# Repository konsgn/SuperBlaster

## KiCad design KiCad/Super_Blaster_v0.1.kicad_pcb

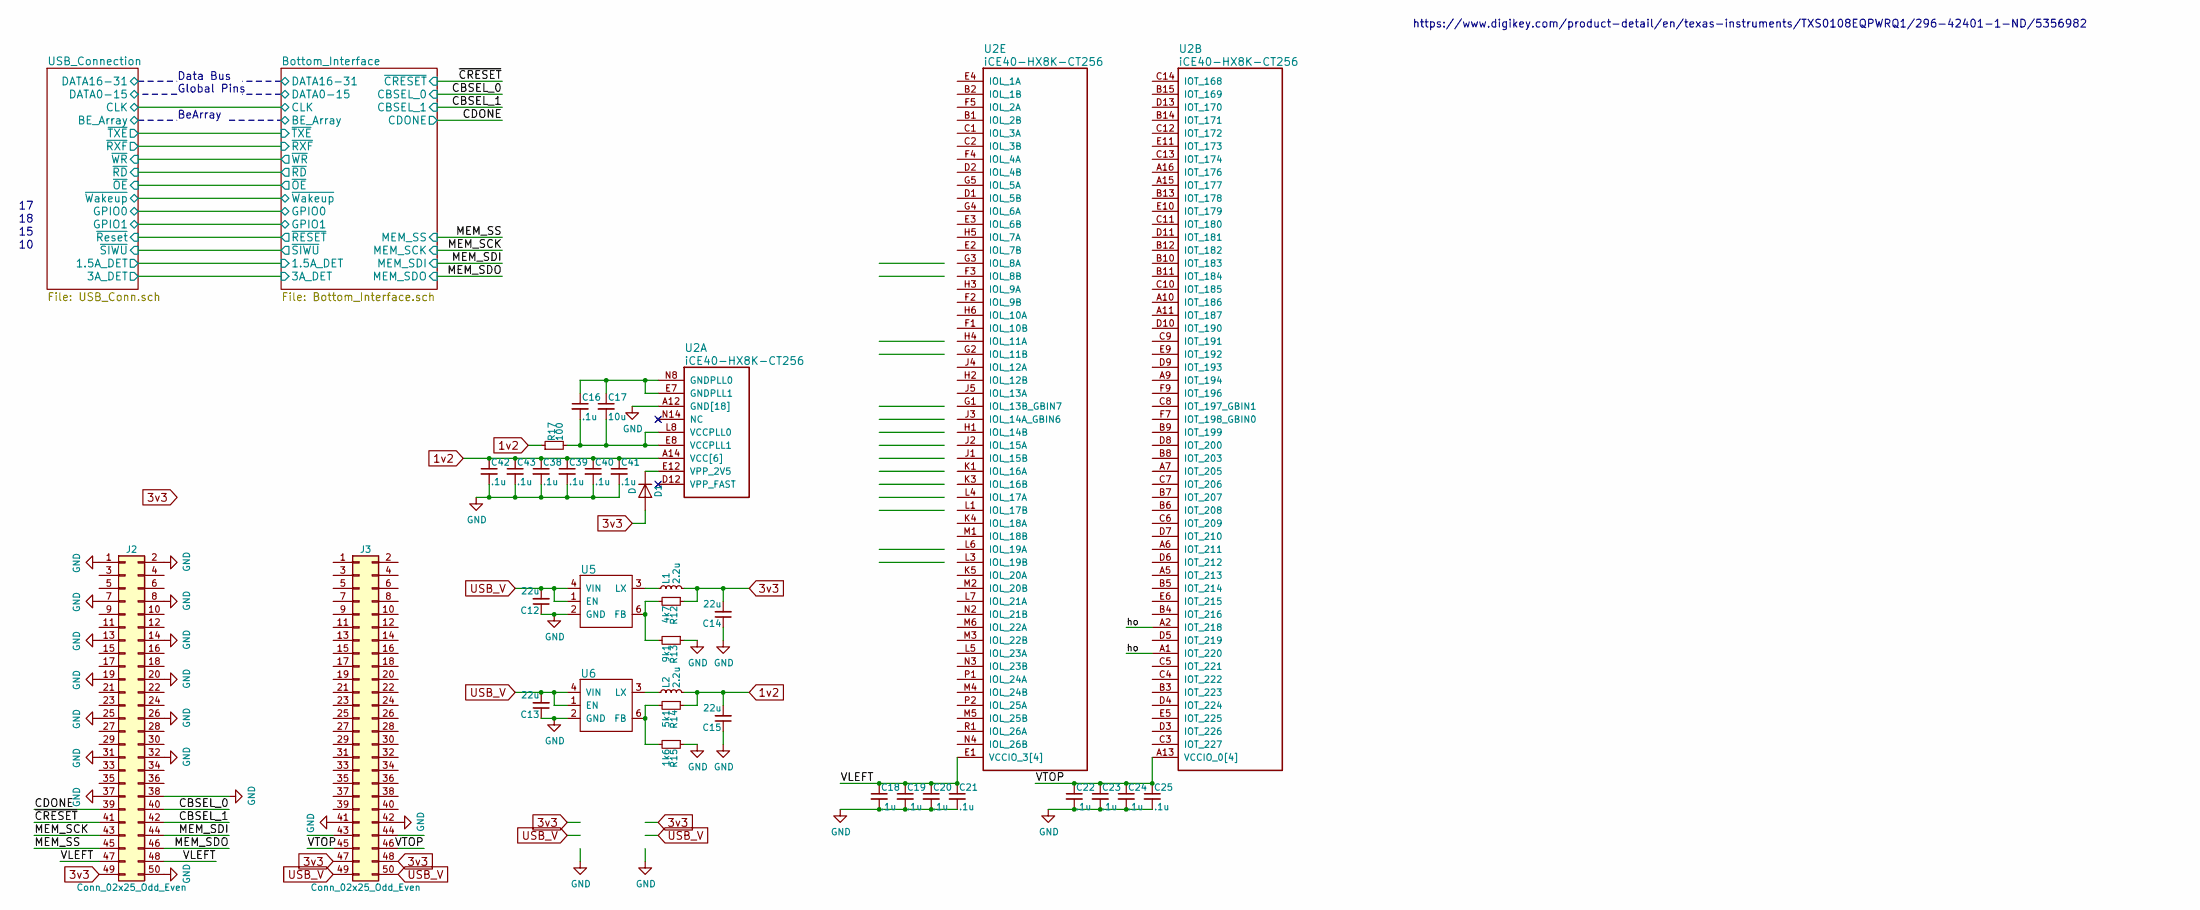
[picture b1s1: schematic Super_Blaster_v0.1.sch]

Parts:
C12, C13, C14, C15: 22u; C_0603
C16, C18, C19, C20, C21, C22, C23, C24, C25, C38, C39, C40, C41, C42, C43: .1u; C_0402_NoSilk
C17: 10u; C_0603
D1: D; D_0402_1005Metric
J2, J3: Conn_02x25_Odd_Even; Pin_Header_Straight_2x25_Pitch1.27mm_tight_SMD
L1, L2: 2.2u; L_1008
R12: 4k7; R_0402
R13: 9k1; R_0402
R14: 5k1; R_0402
R15: 1k6; R_0402
R17: 100; R_0603
U2: iCE40-HX8K-CT256; caBGA_256_.8p_14x14mm
U5, U6: REG_EN_GND_LX_VIN_NC_FB; TSOT-23-6

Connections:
1v2: C15.2, C38.1, C39.1, C40.1, C41.1, C42.1, C43.1, L2.2, R14.1, R17.1, U2.A14 (VCC[6]), U2.F6 (VCC[6]), U2.F10 (VCC[6]), U2.K6 (VCC[6]), U2.K10 (VCC[6]), U2.L2 (VCC[6])
3v3: C14.2, D1.2 (A), J2.49, J3.47, J3.48, L1.2, R12.1; also elsewhere on the board
/CBSEL_0: J2.40; also elsewhere on the board
/CBSEL_1: J2.42; also elsewhere on the board
/CDONE: J2.39; also elsewhere on the board
/MEM_SCK: J2.43; also elsewhere on the board
/MEM_SDI: J2.44; also elsewhere on the board
/MEM_SDO: J2.46; also elsewhere on the board
/MEM_SS: J2.45; also elsewhere on the board
/VLEFT: C18.1, C19.1, C20.1, C21.1, J2.47, J2.48, U2.E1 (VCCIO_3[4]), U2.G6 (VCCIO_3[4]), U2.J6 (VCCIO_3[4]), U2.N1 (VCCIO_3[4])
/VTOP: C22.1, C23.1, C24.1, C25.1, J3.45, J3.46, U2.A3 (VCCIO_0[4]), U2.A8 (VCCIO_0[4]), U2.A13 (VCCIO_0[4]), U2.F8 (VCCIO_0[4])
/ho: U2.A1 (IOT_220), U2.A2 (IOT_218)
/~CRESET: J2.41; also elsewhere on the board
GND: C12.1, C13.1, C14.1, C15.1, C18.2, C19.2, C20.2, C21.2, C22.2, C23.2, C24.2, C25.2, C38.2, C39.2, C40.2, C41.2, C42.2, C43.2, J2.1, J2.2, J2.7, J2.8, J2.13, J2.14, J2.19, J2.20, J2.25, J2.26, J2.31, J2.32, J2.37, J2.38, J2.50, J3.41, J3.42, R13.1, R15.1, U2.A4 (GND[18]), U2.A12 (GND[18]), U2.E15 (GND[18]), U2.G7 (GND[18]), U2.G8 (GND[18]), U2.G9 (GND[18]), U2.H7 (GND[18]), U2.H8 (GND[18]), U2.H9 (GND[18]), U2.J7 (GND[18]), U2.J8 (GND[18]), U2.J9 (GND[18]), U2.K2 (GND[18]), U2.K7 (GND[18]), U2.L15 (GND[18]), U2.R7 (GND[18]), U2.T4 (GND[18]), U2.T12 (GND[18]), U5.2 (GND), U6.2 (GND); also elsewhere on the board
unnamed: C16.1, C17.1, U2.E7 (GNDPLL1), U2.N8 (GNDPLL0)
unnamed: C16.2, C17.2, R17.2, U2.E8 (VCCPLL1), U2.L8 (VCCPLL0)
unnamed: D1.1 (K), U2.E12 (VPP_2V5)
unnamed: L1.1, U5.3 (LX)
unnamed: L2.1, U6.3 (LX)
unnamed: R12.2, R13.2, U5.6 (FB)
unnamed: R14.2, R15.2, U6.6 (FB)
USB_V: C12.2, C13.2, J3.49, J3.50, U5.1 (EN), U5.4 (VIN), U6.1 (EN), U6.4 (VIN); also elsewhere on the board

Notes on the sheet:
BeArray
Data Bus Global Pins
https://www.digikey.com/product-detail/en/texas-instruments/TXS0108EQPWRQ1/296-42401-1-ND/5356982

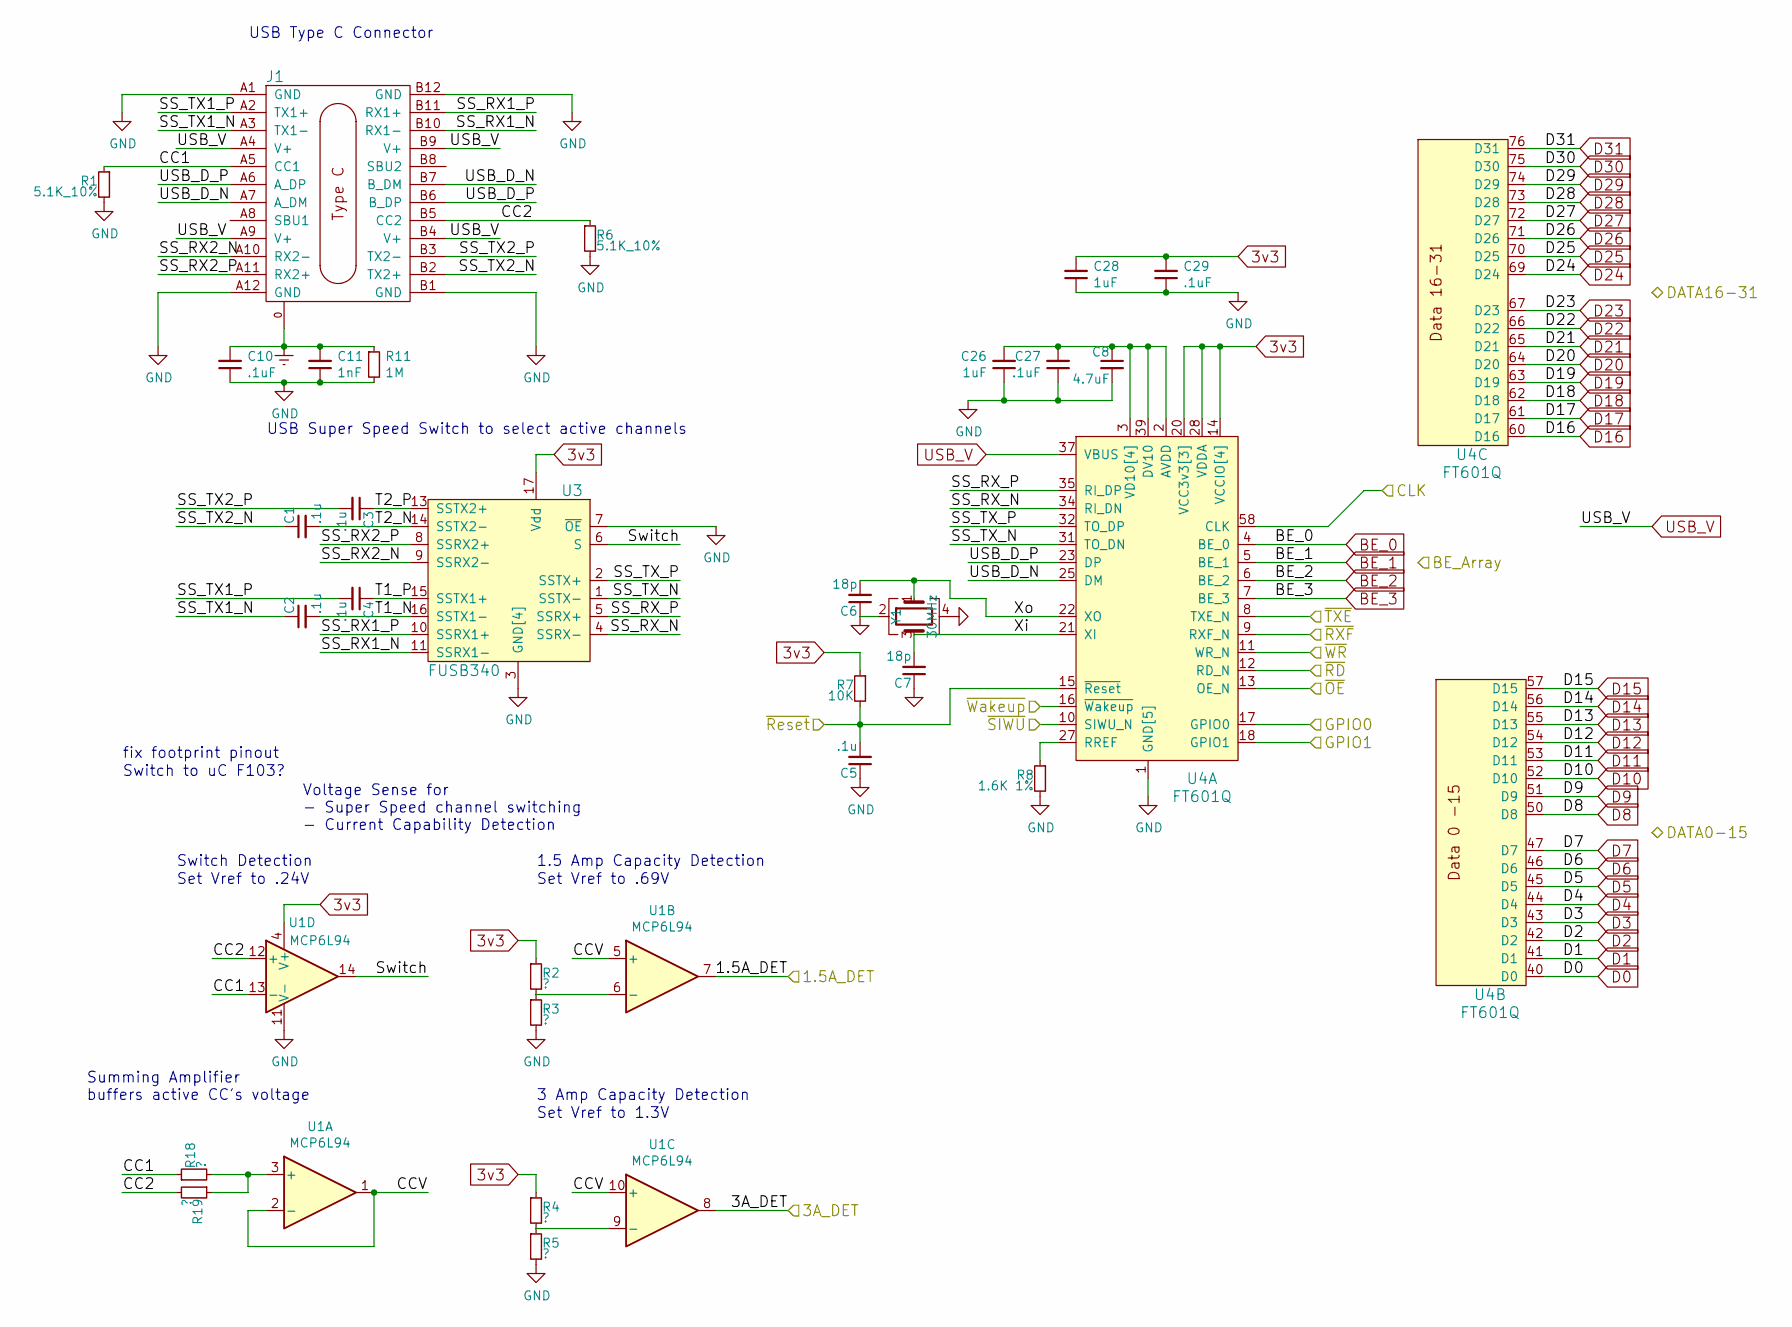
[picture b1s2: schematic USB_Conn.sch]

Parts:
C1, C2, C3, C4, C5: .1u; C_0402
C6, C7: 18p; C_0402
C8: 4.7uF; C_0603
C10, C27, C29: .1uF; C_0402
C11: 1nF; C_0402
C26, C28: 1uF; C_0402
J1: USB_TypeC_AMP_12401610E4#2A; USB_TypeC_Right_Angle_SMD_THT_12401610E4#2A
R1, R6: 5.1K_10%; R_0402
R2, R3, R4, R5, R18, R19: ?; R_0402
R7: 10K; R_0402
R8: 1.6K 1%; R_0402
R11: 1M; R_0402
U1: MCP6L94; SSOP-14
U3: FUSB340; FUSB340_Custom
U4: FT601Q; QFN_76_PAD
Y1: 30MHz; Crystal_SMD_2016-4Pin_2.0x1.6mm; MPN XRCGB30M000F3M00R0

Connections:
3v3: C28.2, C29.2, R2.1, R4.1, R7.1, U1.4 (V+), U3.17 (Vdd), U4.14 (VCCIO[4]), U4.20 (VCC3v3[3]), U4.24 (VCC3v3), U4.28 (VDDA), U4.38 (VCC3v3), U4.49 (VCCIO), U4.59 (VCCIO), U4.68 (VCCIO); also elsewhere on the board
/Bottom_Interface/1.5A_DET: U1.7; also elsewhere on the board
/Bottom_Interface/3A_DET: U1.8; also elsewhere on the board
/Bottom_Interface/CLK: U4.58 (CLK); also elsewhere on the board
/Bottom_Interface/GPIO0: U4.17 (GPIO0); also elsewhere on the board
/Bottom_Interface/GPIO1: U4.18 (GPIO1); also elsewhere on the board
/Bottom_Interface/~OE: U4.13 (OE_N); also elsewhere on the board
/Bottom_Interface/~RD: U4.12 (RD_N); also elsewhere on the board
/Bottom_Interface/~RESET: C5.2, R7.2, U4.15 (~Reset); also elsewhere on the board
/Bottom_Interface/~RXF: U4.9 (RXF_N); also elsewhere on the board
/Bottom_Interface/~SIWU: U4.10 (SIWU_N); also elsewhere on the board
/Bottom_Interface/~TXE: U4.8 (TXE_N); also elsewhere on the board
/Bottom_Interface/~WR: U4.11 (WR_N); also elsewhere on the board
/Bottom_Interface/~Wakeup: U4.16 (~Wakeup); also elsewhere on the board
/USB_Connection/CC1: J1.A5 (CC1), R1.1, R18.1, U1.13 (-)
/USB_Connection/CC2: J1.B5 (CC2), R6.1, R19.2, U1.12 (+)
/USB_Connection/CCV: U1.1, U1.2 (-), U1.5 (+), U1.10 (+)
/USB_Connection/SS_RX1_N: J1.B10 (RX1-), U3.11 (SSRX1-)
/USB_Connection/SS_RX1_P: J1.B11 (RX1+), U3.10 (SSRX1+)
/USB_Connection/SS_RX2_N: J1.A10 (RX2-), U3.9 (SSRX2-)
/USB_Connection/SS_RX2_P: J1.A11 (RX2+), U3.8 (SSRX2+)
/USB_Connection/SS_RX_N: U3.4 (SSRX-), U4.34 (RI_DN)
/USB_Connection/SS_RX_P: U3.5 (SSRX+), U4.35 (RI_DP)
/USB_Connection/SS_TX1_N: C2.1, J1.A3 (TX1-)
/USB_Connection/SS_TX1_P: C4.2, J1.A2 (TX1+)
/USB_Connection/SS_TX2_N: C1.1, J1.B2 (TX2+)
/USB_Connection/SS_TX2_P: C3.2, J1.B3 (TX2-)
/USB_Connection/SS_TX_N: U3.1 (SSTX-), U4.31 (TO_DN)
/USB_Connection/SS_TX_P: U3.2 (SSTX+), U4.32 (TO_DP)
/USB_Connection/Switch: U1.14, U3.6 (S)
/USB_Connection/T1_N: C2.2, U3.16 (SSTX1-)
/USB_Connection/T1_P: C4.1, U3.15 (SSTX1+)
/USB_Connection/T2_N: C1.2, U3.14 (SSTX2-)
/USB_Connection/T2_P: C3.1, U3.13 (SSTX2+)
/USB_Connection/USB_D_N: J1.A7 (A_DM), J1.B7 (B_DM), U4.25 (DM)
/USB_Connection/USB_D_P: J1.A6 (A_DP), J1.B6 (B_DP), U4.23 (DP)
/USB_Connection/Xi: C7.2, U4.21 (XI), Y1.3
/USB_Connection/Xo: C6.2, U4.22 (XO), Y1.1
BE_0: U4.4 (BE_0); also elsewhere on the board
BE_1: U4.5 (BE_1); also elsewhere on the board
BE_2: U4.6 (BE_2); also elsewhere on the board
BE_3: U4.7 (BE_3); also elsewhere on the board
D0: U4.40 (D0); also elsewhere on the board
D1: U4.41 (D1); also elsewhere on the board
D2: U4.42 (D2); also elsewhere on the board
D3: U4.43 (D3); also elsewhere on the board
D4: U4.44 (D4); also elsewhere on the board
D5: U4.45 (D5); also elsewhere on the board
D6: U4.46 (D6); also elsewhere on the board
D7: U4.47 (D7); also elsewhere on the board
D8: U4.50 (D8); also elsewhere on the board
D9: U4.51 (D9); also elsewhere on the board
D10: U4.52 (D10); also elsewhere on the board
D11: U4.53 (D11); also elsewhere on the board
D12: U4.54 (D12); also elsewhere on the board
D13: U4.55 (D13); also elsewhere on the board
D14: U4.56 (D14); also elsewhere on the board
D15: U4.57 (D15); also elsewhere on the board
D16: U4.60 (D16); also elsewhere on the board
D17: U4.61 (D17); also elsewhere on the board
D18: U4.62 (D18); also elsewhere on the board
D19: U4.63 (D19); also elsewhere on the board
D20: U4.64 (D20); also elsewhere on the board
D21: U4.65 (D21); also elsewhere on the board
D22: U4.66 (D22); also elsewhere on the board
D23: U4.67 (D23); also elsewhere on the board
D24: U4.69 (D24); also elsewhere on the board
D25: U4.70 (D25); also elsewhere on the board
D26: U4.71 (D26); also elsewhere on the board
D27: U4.72 (D27); also elsewhere on the board
D28: U4.73 (D28); also elsewhere on the board
D29: U4.74 (D29); also elsewhere on the board
D30: U4.75 (D30); also elsewhere on the board
D31: U4.76 (D31); also elsewhere on the board
Earth: C10.2, C11.2, J1.0, R11.1
GND: C5.1, C6.1, C7.1, C8.2, C10.1, C11.1, C26.1, C27.1, C28.1, C29.1, J1.A1 (GND), J1.A12 (GND), J1.B1 (GND), J1.B12 (GND), R1.2, R3.2, R5.2, R6.2, R8.2, R11.2, U1.11 (V-), U3.3 (GND[4]), U3.7 (~OE), U3.12 (GND[4]), U3.18 (GND[4]), U3.PAD (GND[4]), U4.1 (GND[5]), U4.26 (GND), U4.29 (GND), U4.36 (GND), U4.77 (GND), Y1.2, Y1.4; also elsewhere on the board
unnamed: R2.2, R3.1, U1.6 (-)
unnamed: R4.2, R5.1, U1.9 (-)
unnamed: R8.1, U4.27 (RREF)
unnamed: R18.2, R19.1, U1.3 (+)
USB_V: J1.A4 (V+), J1.A9 (V+), J1.B4 (V+), J1.B9 (V+), U4.37 (VBUS); also elsewhere on the board
VD10: C8.1, C26.2, C27.2, U4.2 (AVDD), U4.3 (VD10[4]), U4.30 (VD10), U4.33 (VD10), U4.39 (DV10), U4.48 (VD10)

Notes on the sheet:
USB Type C Connector
USB Super Speed Switch to select active channels
Voltage Sense for - Super Speed channel switching - Current Capability Detection
Switch Detection
1.5 Amp Capacity Detection
3 Amp Capacity Detection
Set Vref to .69V
Set Vref to 1.3V
Set Vref to .24V
fix footprint pinout
Switch to uC F103?
Summing Amplifier buffers active CC's voltage

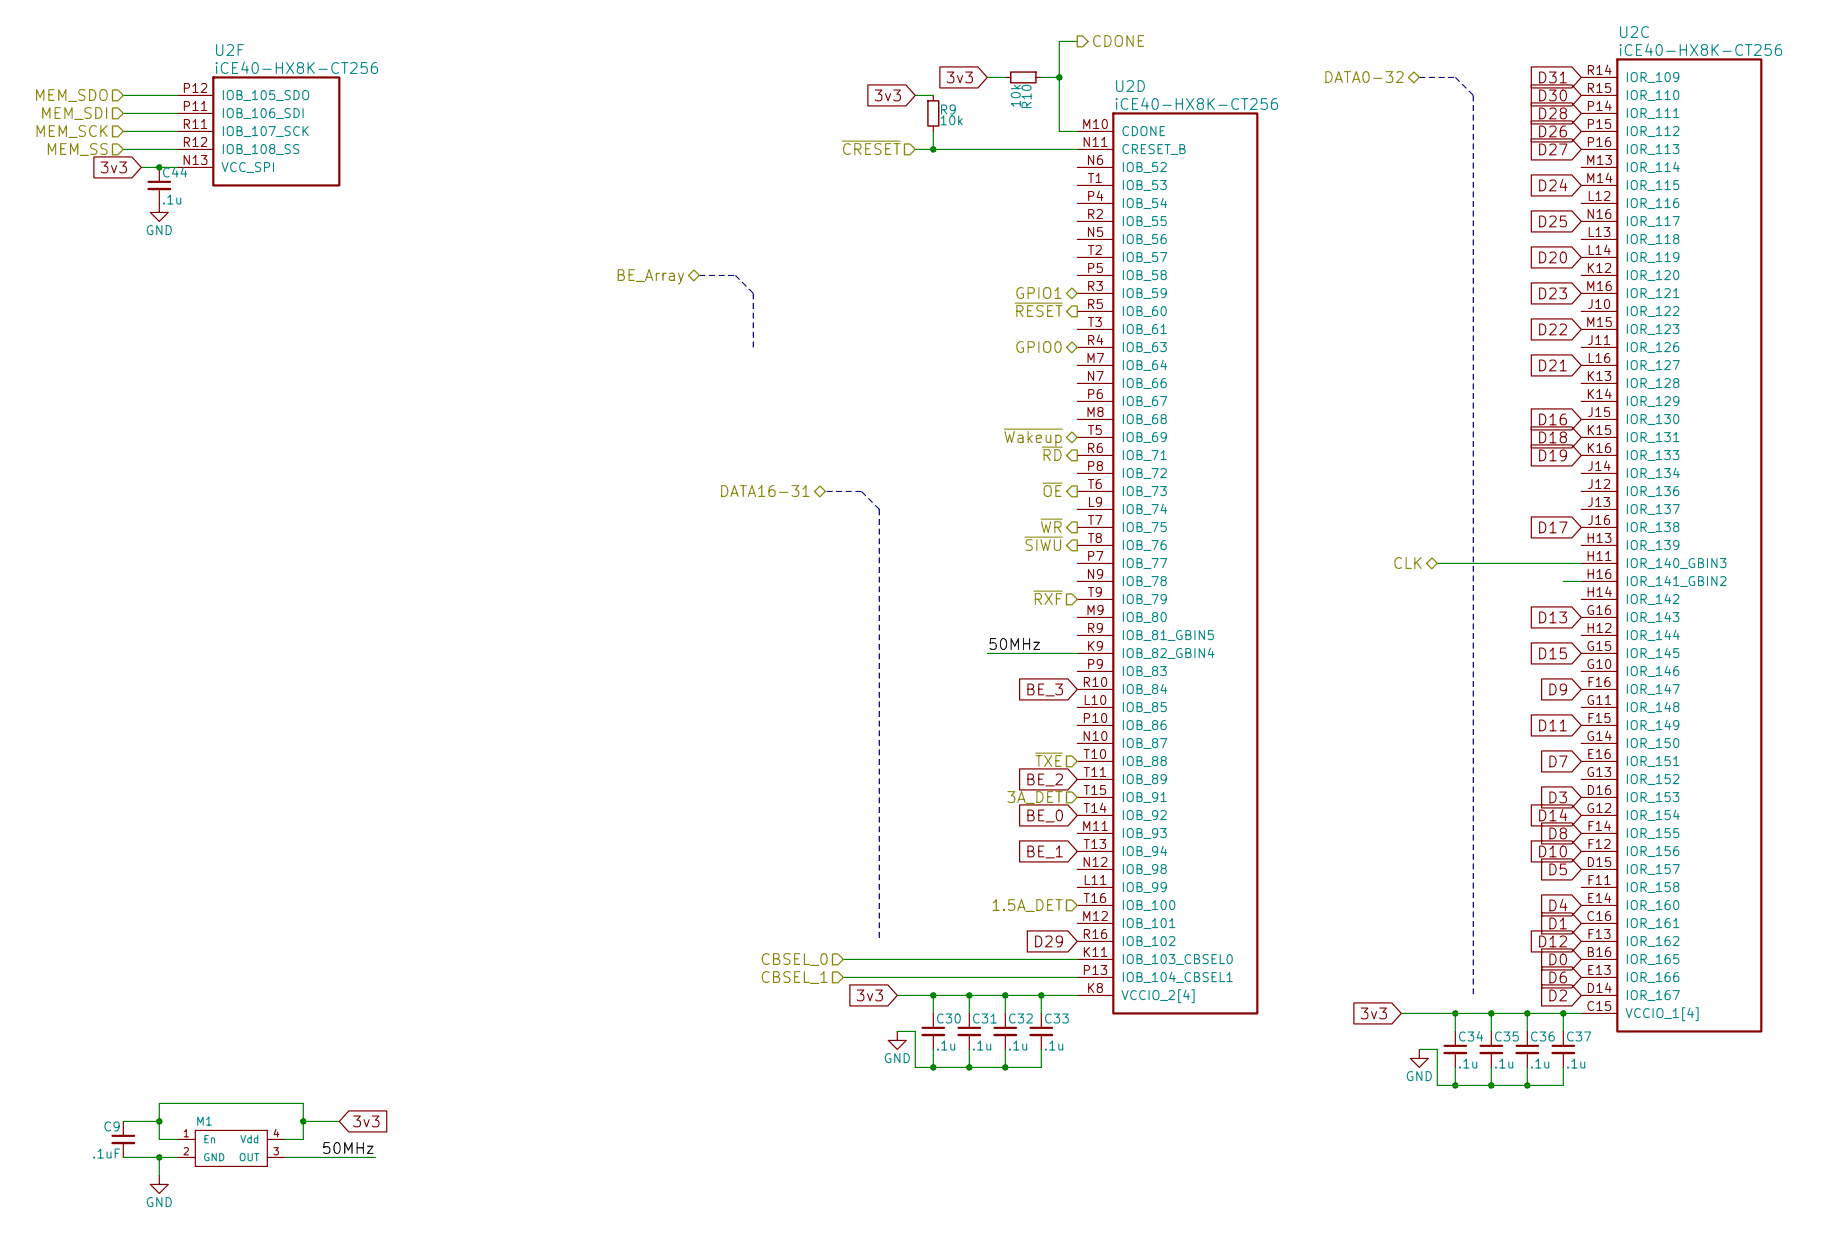
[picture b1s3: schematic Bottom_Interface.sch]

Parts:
C9: .1uF; C_0402
C30, C31, C32, C33, C34, C35, C36, C37, C44: .1u; C_0402_NoSilk
M1: CLOCK_EN; Crystal_SMD_2520-4Pin_2.5x2.0mm
R9, R10: 10k; R_0402
U2: iCE40-HX8K-CT256; caBGA_256_.8p_14x14mm

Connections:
3v3: C9.1, C30.1, C31.1, C32.1, C33.1, C34.1, C35.1, C36.1, C37.1, C44.1, M1.1 (En), M1.4 (Vdd), R9.1, R10.2, U2.C15 (VCCIO_1[4]), U2.H10 (VCCIO_1[4]), U2.H15 (VCCIO_1[4]), U2.K8 (VCCIO_2[4]), U2.N13 (VCC_SPI), U2.N15 (VCCIO_1[4]), U2.P3 (VCCIO_2[4]), U2.R8 (VCCIO_2[4]), U2.R13 (VCCIO_2[4]); also elsewhere on the board
/Bottom_Interface/1.5A_DET: U2.T16 (IOB_100); also elsewhere on the board
/Bottom_Interface/3A_DET: U2.T15 (IOB_91); also elsewhere on the board
/Bottom_Interface/50MHz: M1.3 (OUT), U2.K9 (IOB_82_GBIN4)
/Bottom_Interface/CLK: U2.H11 (IOR_140_GBIN3); also elsewhere on the board
/Bottom_Interface/GPIO0: U2.R4 (IOB_63); also elsewhere on the board
/Bottom_Interface/GPIO1: U2.R3 (IOB_59); also elsewhere on the board
/Bottom_Interface/~OE: U2.T6 (IOB_73); also elsewhere on the board
/Bottom_Interface/~RD: U2.R6 (IOB_71); also elsewhere on the board
/Bottom_Interface/~RESET: U2.R5 (IOB_60); also elsewhere on the board
/Bottom_Interface/~RXF: U2.T9 (IOB_79); also elsewhere on the board
/Bottom_Interface/~SIWU: U2.T8 (IOB_76); also elsewhere on the board
/Bottom_Interface/~TXE: U2.T10 (IOB_88); also elsewhere on the board
/Bottom_Interface/~WR: U2.T7 (IOB_75); also elsewhere on the board
/Bottom_Interface/~Wakeup: U2.T5 (IOB_69); also elsewhere on the board
/CBSEL_0: U2.K11 (IOB_103_CBSEL0); also elsewhere on the board
/CBSEL_1: U2.P13 (IOB_104_CBSEL1); also elsewhere on the board
/CDONE: R10.1, U2.M10 (CDONE); also elsewhere on the board
/MEM_SCK: U2.R11 (IOB_107_SCK); also elsewhere on the board
/MEM_SDI: U2.P11 (IOB_106_SDI); also elsewhere on the board
/MEM_SDO: U2.P12 (IOB_105_SDO); also elsewhere on the board
/MEM_SS: U2.R12 (IOB_108_SS); also elsewhere on the board
/~CRESET: R9.2, U2.N11 (CRESET_B); also elsewhere on the board
BE_0: U2.T14 (IOB_92); also elsewhere on the board
BE_1: U2.T13 (IOB_94); also elsewhere on the board
BE_2: U2.T11 (IOB_89); also elsewhere on the board
BE_3: U2.R10 (IOB_84); also elsewhere on the board
D0: U2.B16 (IOR_165); also elsewhere on the board
D1: U2.C16 (IOR_161); also elsewhere on the board
D2: U2.D14 (IOR_167); also elsewhere on the board
D3: U2.D16 (IOR_153); also elsewhere on the board
D4: U2.E14 (IOR_160); also elsewhere on the board
D5: U2.D15 (IOR_157); also elsewhere on the board
D6: U2.E13 (IOR_166); also elsewhere on the board
D7: U2.E16 (IOR_151); also elsewhere on the board
D8: U2.F14 (IOR_155); also elsewhere on the board
D9: U2.F16 (IOR_147); also elsewhere on the board
D10: U2.F12 (IOR_156); also elsewhere on the board
D11: U2.F15 (IOR_149); also elsewhere on the board
D12: U2.F13 (IOR_162); also elsewhere on the board
D13: U2.G16 (IOR_143); also elsewhere on the board
D14: U2.G12 (IOR_154); also elsewhere on the board
D15: U2.G15 (IOR_145); also elsewhere on the board
D16: U2.J15 (IOR_130); also elsewhere on the board
D17: U2.J16 (IOR_138); also elsewhere on the board
D18: U2.K15 (IOR_131); also elsewhere on the board
D19: U2.K16 (IOR_133); also elsewhere on the board
D20: U2.L14 (IOR_119); also elsewhere on the board
D21: U2.L16 (IOR_127); also elsewhere on the board
D22: U2.M15 (IOR_123); also elsewhere on the board
D23: U2.M16 (IOR_121); also elsewhere on the board
D24: U2.M14 (IOR_115); also elsewhere on the board
D25: U2.N16 (IOR_117); also elsewhere on the board
D26: U2.P15 (IOR_112); also elsewhere on the board
D27: U2.P16 (IOR_113); also elsewhere on the board
D28: U2.P14 (IOR_111); also elsewhere on the board
D29: U2.R16 (IOB_102); also elsewhere on the board
D30: U2.R15 (IOR_110); also elsewhere on the board
D31: U2.R14 (IOR_109); also elsewhere on the board
GND: C9.2, C30.2, C31.2, C32.2, C33.2, C34.2, C35.2, C36.2, C37.2, C44.2, M1.2 (GND); also elsewhere on the board

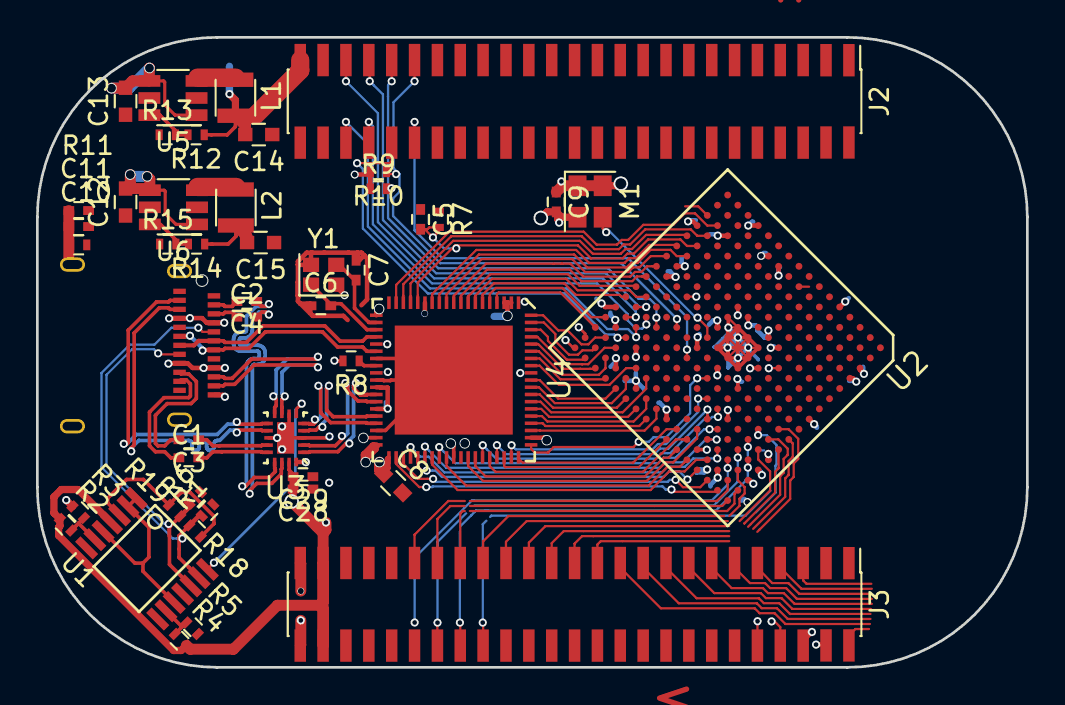
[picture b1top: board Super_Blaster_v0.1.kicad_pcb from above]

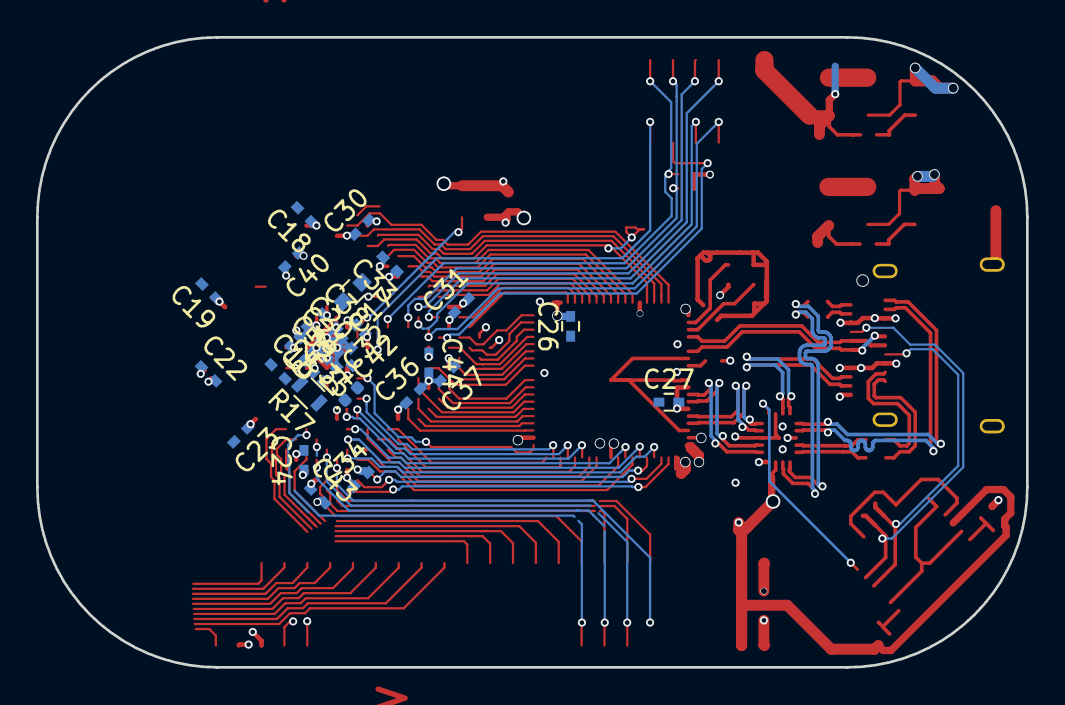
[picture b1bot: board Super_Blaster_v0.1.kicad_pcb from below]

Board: 4 copper layers, 55.0 x 35.0 mm, 76 parts (29 on the bottom side), 102 nets.

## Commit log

2017-04-27 Started Connections
2017-04-28 added current sense&switch
2017-05-01 more sheets
2017-05-02 added connections
2017-05-03 working on bottom FPGA
2017-05-08 fix bus route
2017-06-14 top routed?
2017-10-20 10_20_2017 update
2017-12-12 12_11_17 update
2018-04-20 switch to beaglepocket outline
2018-04-21 updates & Bottom sch recovery
2018-04-30 4_30_updates
2018-07-10 7_6_2018 changes
2018-08-20 updated to v5
2019-01-12 refreshing memory...
